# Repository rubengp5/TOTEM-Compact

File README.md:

> [!WARNING]
> Work In Progress

***

<picture align="center">
  <source media="(prefers-color-scheme: dark)" srcset="/docs/images/TOTEM_logo_dark.svg">
  <source media="(prefers-color-scheme: light)" srcset="/docs/images/TOTEM_logo_bright.svg">
  
</picture>

<h1 align="center">T O T E M</h1>

TOTEM is a 38 key column-staggered choc split keyboard. It is meant to be used with a [Seeed Studio XIAO nRF52840 BLE](https://www.seeedstudio.com/Seeed-XIAO-BLE-nRF52840-p-5201.html) or [XIAO RP2040](https://www.seeedstudio.com/XIAO-RP2040-v1-0-p-5026.html).
It was created for the SEEED XIAO keyboard contest.\
[Here](https://www.hackster.io/geist/totem-a-tiny-splitkeyboard-with-splay-cb2e43) you can read about the process of making it.

***

## LAYOUT

***

## PCB

[Here](/PCB/) you can find the KiCad files and Gerbers for the TOTEM.

***

## CASE

You can use the TOTEM without a case, but [here](/case/) you can find one I made for it.

***

## BUILD GUIDE

The build guide for the TOTEM can be found [here](/docs/buildguide.md).

***

## FIRMWARE

[QMK (VIAL) precompiled](/firmware/QMK/) or [QMK (VIAL) source](/firmware/QMK/VIAL_source/) for the TOTEM (wired using the XIAO RP2040)\
[ZMK precompiled](/firmware/ZMK/) or [ZMK source (outdated)](https://github.com/GEIGEIGEIST/zmk-config-totem) for the TOTEM (wireless using the XIAO BLE)

***

## BUY

You can buy TOTEM kits and finished builds on [keeb.supply](https://keeb.supply/products/geist-totem) (based in Germany)

***

## PHOTOS

This is the TOTEM in a black resin case

\
\

This is the TOTEM with a black resin tenting bottom plate

\
[Video by *Wolfgang's Channel* showing the tenting system in action](https://youtu.be/rvM2BthjEI4?si=mTJVdPeZstshnDyo)

***

## CREDITS

### INSPIRATION

I've added the additional pinky key to make the TOTEM compatible with the layout boards like the [Balbuzard](https://github.com/brow/balbuzard) by [Tom Brow](https://github.com/brow) and the [Osprette](https://github.com/smores56/osprette) by [Sam Mohr](https://github.com/smores56) use, where you put the keybinding of the top left and right keys on an outer pinky key.

### HELP FIXING THINGS

People who helped me create this board and fix stuff

#### PCB
- [Marco "Bob"](https://github.com/GroooveBob)

#### CASE
- [Freya](https://github.com/freya-irl)
- [Bubbleology](https://github.com/bubbleology)

#### FIRMWARE
- [Cem Aksoylar](https://github.com/caksoylar)
- [Grinnie](https://github.com/regicidalplutophage)
- [Alaa Saad Mansour](https://github.com/AlaaSaadAbdo)
- [pekudzu](https://github.com/pekudzu)

If you build a TOTEM I would be pretty happy to see some pictures. And if you want to leave me a tip you can do this [here](https://ko-fi.com/geigeigeist) (but please don't feel pressured)

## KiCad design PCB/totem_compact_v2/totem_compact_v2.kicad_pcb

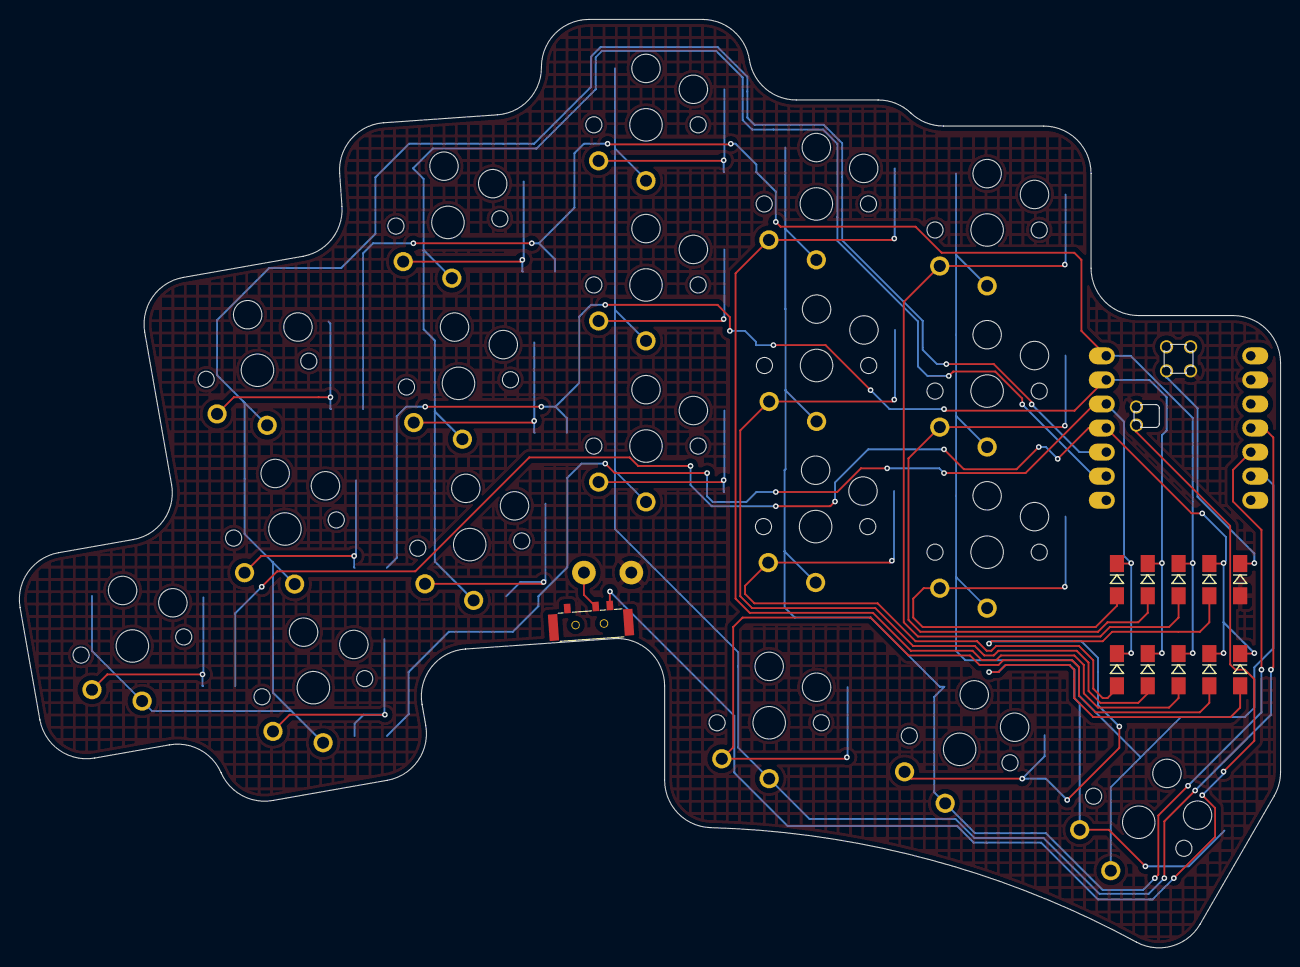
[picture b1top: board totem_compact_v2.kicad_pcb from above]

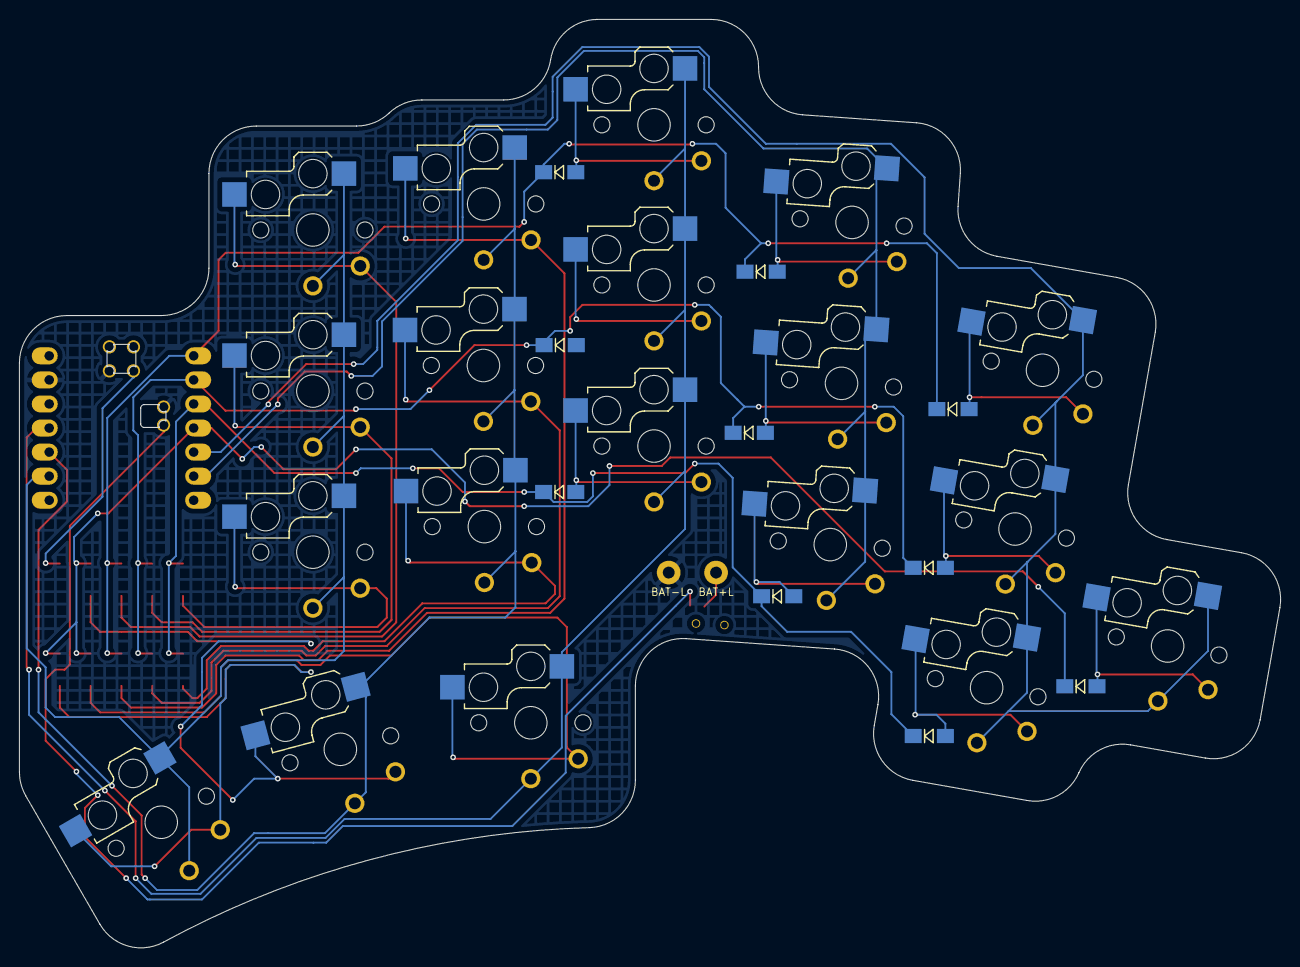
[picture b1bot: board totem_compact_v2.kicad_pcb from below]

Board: 2 copper layers, 133.1 x 98.0 mm, 43 parts (10 on the bottom side), 32 nets.

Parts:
BAT+1L1: BAT+L; BatteryPad
BAT-1L1: BAT-L; BatteryPad
DL1, DL2, DL3, DL4, DL5, DL6, DL7, DL8, DL9, DL10, DL11, DL12, DL13, DL14, DL15, DL16, DL17, DL18, DL19: D_Small; Diode_SOD123
LSW1: SW_Push; Diode_SOD123
LSW2: SW_SPDT; MSK12C02
SWL1, SWL2, SWL3, SWL4, SWL5, SWL6, SWL7, SWL8, SWL9, SWL10, SWL11, SWL12, SWL13, SWL14, SWL15, SWL16, SWL17, SWL18, SWL19: SW_Push_45deg; Kailh_socket_PG1350_optional
U1: xiao-ble; xiao-ble-smd-cutout

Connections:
BAT+L: LSW2.3 (C), U1.19 (BAT)
COL0_L: SWL1.1, SWL6.1, SWL11.1, SWL16.1, U1.5 (A8_SDA/0.04_H)
COL1_L: SWL2.1, SWL7.1, SWL12.1, U1.6 (A9_SCL/0.05_H)
COL2_L: SWL3.1, SWL8.1, SWL13.1, SWL17.1, U1.11 (A6_MOSI/1.15)
COL3_L: SWL4.1, SWL9.1, SWL14.1, SWL18.1, U1.10 (A5_MISO/1.14)
COL4_L: SWL5.1, SWL10.1, SWL15.1, SWL19.1, U1.9 (A7_SCK/1.13)
GND_L: BAT-1L1.1, LSW1.2, U1.13 (GND), U1.18 (GND), U1.20 (GND)
unnamed: DL1.2 (A), SWL1.2
unnamed: DL2.2 (A), SWL2.2
unnamed: DL3.2 (A), SWL3.2
unnamed: DL4.2 (A), SWL4.2
unnamed: DL5.2 (A), SWL5.2
unnamed: DL6.2 (A), SWL6.2
unnamed: DL7.2 (A), SWL7.2
unnamed: DL8.2 (A), SWL8.2
unnamed: DL9.2 (A), SWL9.2
unnamed: DL10.2 (A), SWL10.2
unnamed: DL11.2 (A), SWL11.2
unnamed: DL12.2 (A), SWL12.2
unnamed: DL13.2 (A), SWL13.2
unnamed: DL14.2 (A), SWL14.2
unnamed: DL15.2 (A), SWL15.2
unnamed: DL16.2 (A), SWL16.2
unnamed: DL17.2 (A), SWL17.2
unnamed: DL18.2 (A), SWL18.2
unnamed: DL19.2 (A), SWL19.2
RESET_L: LSW1.1, U1.17 (RESET)
ROW0_L: DL1.1 (K), DL2.1 (K), DL3.1 (K), DL4.1 (K), DL5.1 (K), U1.1 (A2/0.02_H)
ROW1_L: DL6.1 (K), DL7.1 (K), DL8.1 (K), DL9.1 (K), DL10.1 (K), U1.2 (A4/0.03_H)
ROW2_L: DL11.1 (K), DL12.1 (K), DL13.1 (K), DL14.1 (K), DL15.1 (K), U1.3 (A10/0.28)
ROW3_L: DL16.1 (K), DL17.1 (K), DL18.1 (K), DL19.1 (K), U1.4 (A11/0.29)
VBAT_L: BAT+1L1.1, LSW2.2 (B)

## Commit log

2025-11-17 Actualizar README.md
2025-11-18 create compact PCB
2025-11-22 Update PCB
2025-11-22 v2 PCB
